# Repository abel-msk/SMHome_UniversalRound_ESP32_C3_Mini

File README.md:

# SMHome_UniversalRound_ESP32_C3_Mini

This is small pcb board was designed to place  under wall mounted electric components in socket box, 
it steel can bee plcad in its own box  znd powered by usb.

## Haw to use

```
git clone https://github.com/abel-msk/SMHome_UniversalRound_ESP32_C3_Mini.git
cd SMHome_UniversalRound_ESP32_C3_Mini
```
Next step is to open project file  `SMHome_UniversalRound_ESP32_C3_Mini_v3.kicad_pro`  in KiKad. 

## 3D view on top of board

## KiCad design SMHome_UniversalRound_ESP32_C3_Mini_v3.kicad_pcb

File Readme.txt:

Универсальная плата с выводами на Дисплей (SPI),  I2C, и 3х GPIO/ADC

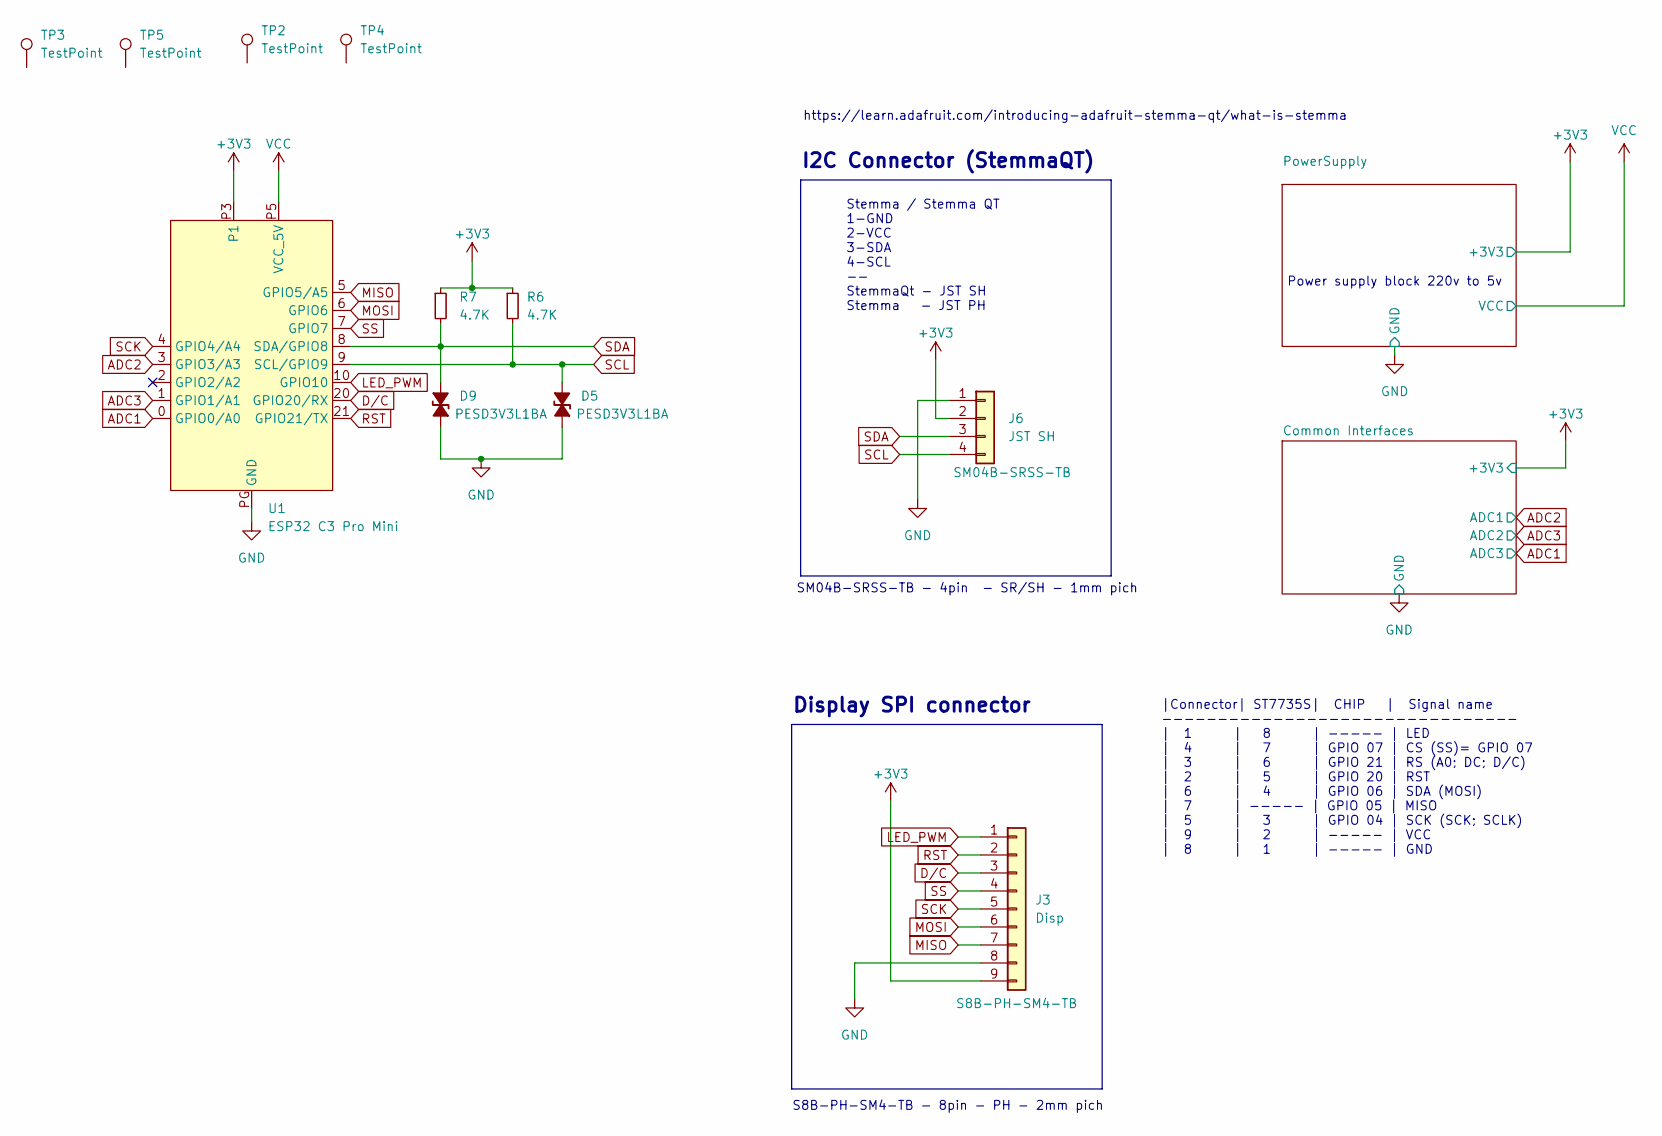
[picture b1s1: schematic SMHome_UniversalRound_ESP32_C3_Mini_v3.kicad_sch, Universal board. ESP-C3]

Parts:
D5, D9: PESD3V3L1BA; D_SOD-323_HandSoldering
J3: Disp; JST_PH_S9B-PH-SM4-TB_1x09-1MP_P2.00mm_Horizontal
J6: JST SH; JST_SH_SM04B-SRSS-TB_1x04-1MP_P1.00mm_Horizontal
R6, R7: 4.7K; R_0805_2012Metric_Pad1.20x1.40mm_HandSolder
TP2, TP3, TP4, TP5: TestPoint; TestPoint_THTPad_D2.0mm_Drill1.0mm
U1: ESP32 C3 Pro Mini; ESP32-C3_Pro_mini_no_keepout

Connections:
+3V3: J3.9, J6.2, R6.1, R7.1, U1.P3 (P1); also elsewhere on the board
ADC1: U1.0 (GPIO0/A0); also elsewhere on the board
ADC2: U1.3 (GPIO3/A3); also elsewhere on the board
ADC3: U1.1 (GPIO1/A1); also elsewhere on the board
D/C: J3.3, U1.20 (GPIO20/RX)
GND: D5.2 (A), D9.2 (A), J3.8, J6.1, U1.PG (GND); also elsewhere on the board
LED_PWM: J3.1, U1.10 (GPIO10)
MISO: J3.7, U1.5 (GPIO5/A5)
MOSI: J3.6, U1.6 (GPIO6)
RST: J3.2, U1.21 (GPIO21/TX)
SCK: J3.5, U1.4 (GPIO4/A4)
SCL: D5.1 (K), J6.4, R6.2, U1.9 (SCL/GPIO9)
SDA: D9.1 (K), J6.3, R7.2, U1.8 (SDA/GPIO8)
SS: J3.4, U1.7 (GPIO7)
VCC: U1.P5 (VCC_5V); also elsewhere on the board

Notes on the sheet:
SM04B-SRSS-TB - 4pin - SR/SH - 1mm pich
Stemma / Stemma QT 1-GND 2-VCC 3-SDA 4-SCL -- StemmaQt - JST SH Stemma - JST PH
Power supply block 220v to 5v
https://learn.adafruit.com/introducing-adafruit-stemma-qt/what-is-stemma
S8B-PH-SM4-TB - 8pin - PH - 2mm pich
I2C Connector (StemmaQT)
|Connector| ST7735S| CHIP | Signal name -------------------------------- | 1 | 8 | ----- | LED | 4 | 7 | GPIO 07 | CS (SS)= GPIO 07 | 3 | 6 | GPIO 21 | RS (A0; DC; D/C) | 2 | 5 | GPIO 20 | RST | 6 | 4 | GPIO 06 | SDA (MOSI) | 7 | ----- | GPIO 05 | MISO | 5 | 3 | GPIO 04 | SCK (SCK; SCLK) | 9 | 2 | 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
Display SPI connector

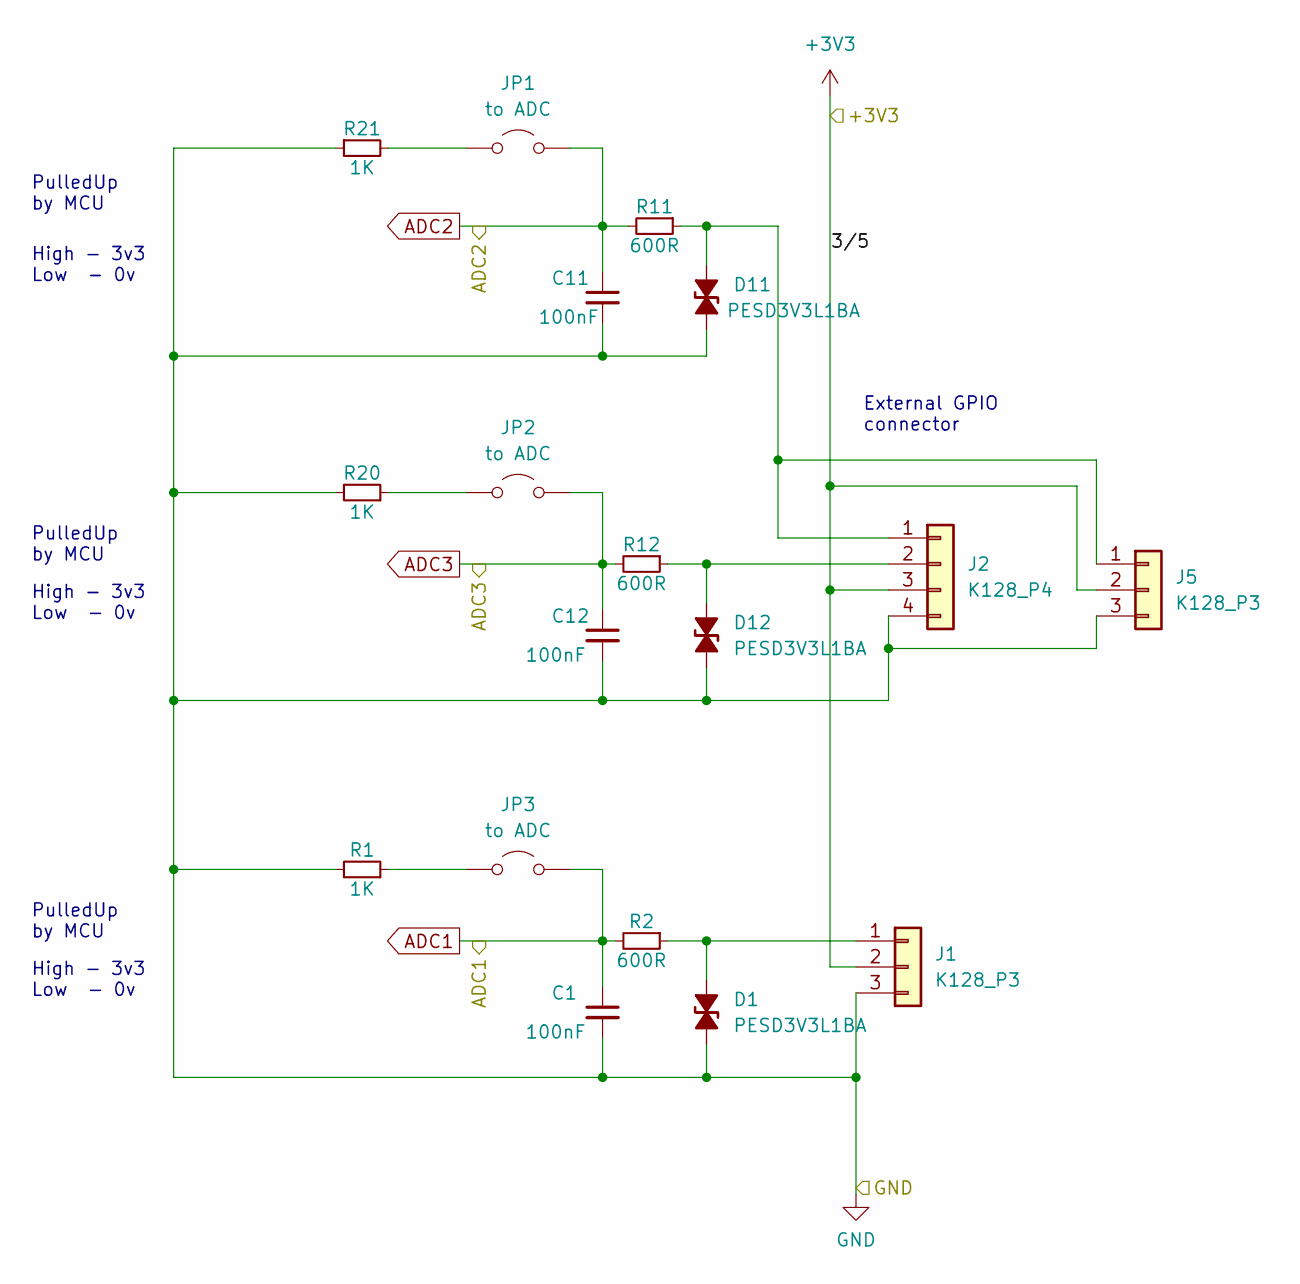
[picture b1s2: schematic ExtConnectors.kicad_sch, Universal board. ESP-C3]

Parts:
C1, C11, C12: 100nF; C_0805_2012Metric
D1, D11, D12: PESD3V3L1BA; D_SOD-323_HandSoldering
J1, J5: K128_P3; PinHeader_1x03_P2.54mm_Vertical
J2: K128_P4; Phoenix Contact_MPT-0,5_4_2,54_P4
JP1, JP2, JP3: to ADC; SolderJumper-2_P1.3mm_Open_TrianglePad1.0x1.5mm
R1, R20, R21: 1K; R_0603_1608Metric_Pad0.98x0.95mm_HandSolder
R2, R11, R12: 600R; R_0603_1608Metric_Pad0.98x0.95mm_HandSolder

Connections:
+3V3: J1.2, J2.3, J5.2; also elsewhere on the board
ADC1: C1.1, JP3.2 (B), R2.2; also elsewhere on the board
ADC2: C11.1, JP1.2 (B), R11.2; also elsewhere on the board
ADC3: C12.1, JP2.2 (B), R12.2; also elsewhere on the board
GND: C1.2, C11.2, C12.2, D1.2 (A), D11.2 (A), D12.2 (A), J1.3, J2.4, J5.3, R1.2, R20.2, R21.1; also elsewhere on the board
unnamed: D1.1 (K), J1.1, R2.1
unnamed: D11.1 (K), J2.1, J5.1, R11.1
unnamed: D12.1 (K), J2.2, R12.1
unnamed: JP1.1 (A), R21.2
unnamed: JP2.1 (A), R20.1
unnamed: JP3.1 (A), R1.1

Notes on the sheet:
External GPIO connector
PulledUp by MCU
High - 3v3 Low - 0v

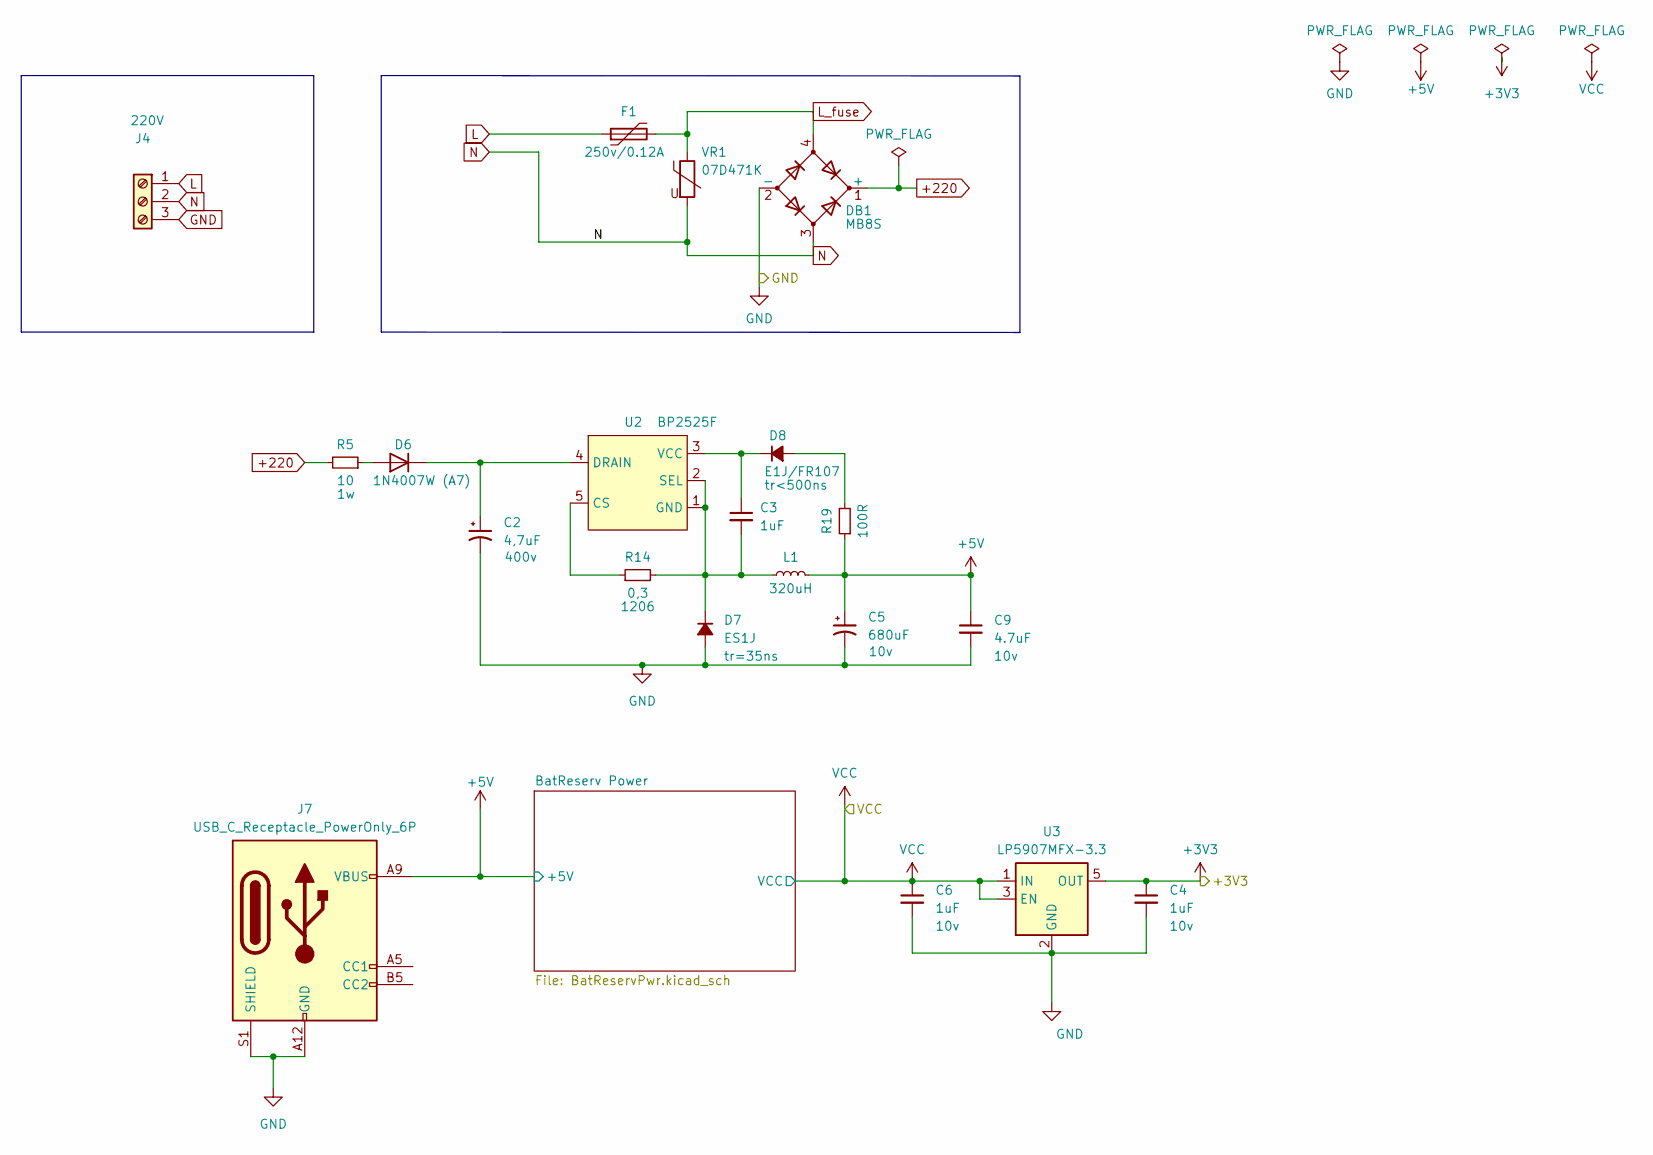
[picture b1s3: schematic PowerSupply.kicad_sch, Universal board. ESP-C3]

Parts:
C2: 4,7uF; CP_Radial_D8.0mm_P3.80mm
C3, C4, C6: 1uF; C_0805_2012Metric_Pad1.18x1.45mm_HandSolder
C5: 680uF; CP_Radial_D6.3mm_P2.50mm
C9: 4.7uF; C_0805_2012Metric_Pad1.18x1.45mm_HandSolder
D6: 1N4007W (A7); D_SOD-123F
D7: ES1J; D_SMA
D8: E1J/FR107; D_SOD-123F
DB1: MB8S; MBS
F1: 250v/0.12A; RF145_D6.5mm_W4mm
J4: 220V; DG301-5.0-03P
J7: USB_C_Receptacle_PowerOnly_6P; USB_C_Receptacle_GCT_USB4125-xx-x_6P_TopMnt_Horizontal
L1: 320uH; L_Radial_D10.0mm_P5.00mm_Fastron_07P
R5: 10; R_Axial_DIN0414_L11.9mm_D4.5mm_P5.08mm_Vertical
R14: 0,3; R_1206_3216Metric_Pad1.30x1.75mm_HandSolder
R19: 100R; R_0805_2012Metric_Pad1.20x1.40mm_HandSolder
U2: BP2525F; SOT33-5
U3: LP5907MFX-3.3; SOT-23-5
VR1: 07D471K; RV_Disc_D9mm_W3.3mm_P5mm

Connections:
+3V3: C4.1, U3.5 (OUT); also elsewhere on the board
+5V: C5.1, C9.1, J7.A9 (VBUS), J7.B9 (VBUS), L1.2, R19.1; also elsewhere on the board
+220: DB1.1 (+), R5.2
GND: C2.2, C4.2, C5.2, C6.2, C9.2, D7.2 (A), DB1.2 (-), J4.3, J7.A12 (GND), J7.B12 (GND), J7.S1 (SHIELD), U3.2 (GND); also elsewhere on the board
L: F1.1, J4.1
L_fuse: DB1.4, F1.2, VR1.1
N: DB1.3, J4.2, VR1.2
unnamed: D6.2 (A), R5.1
unnamed: C2.1, D6.1 (K), U2.4 (DRAIN)
unnamed: C3.2, D7.1 (K), L1.1, R14.2, U2.1 (GND), U2.2 (SEL)
unnamed: D8.2 (A), R19.2
unnamed: C3.1, D8.1 (K), U2.3 (VCC)
unnamed: R14.1, U2.5 (CS)
VCC: C6.1, U3.1 (IN), U3.3 (EN); also elsewhere on the board

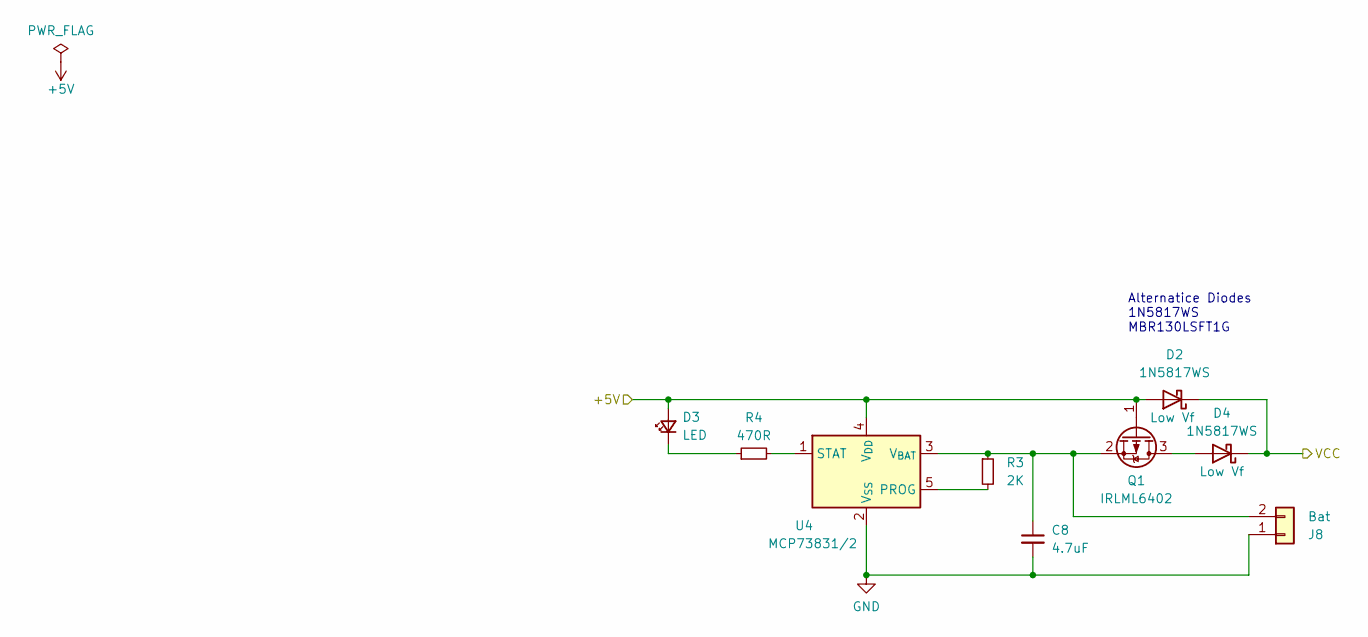
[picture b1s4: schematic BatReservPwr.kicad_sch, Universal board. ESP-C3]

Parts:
C8: 4.7uF; C_0805_2012Metric_Pad1.18x1.45mm_HandSolder
D2, D4: 1N5817WS; D_SOD-123
D3: LED; LED_0603_1608Metric_Pad1.05x0.95mm_HandSolder
J8: Bat; JST_SH_SM02B-SRSS-TB_1x02-1MP_P1.00mm_Horizontal
Q1: IRLML6402; SOT-23
R3: 2K; R_0805_2012Metric_Pad1.20x1.40mm_HandSolder
R4: 470R; R_0805_2012Metric_Pad1.20x1.40mm_HandSolder
U4: MCP73831/2; SOT-23-5

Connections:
+5V: D2.2 (A), D3.2 (A), Q1.1 (G), U4.4 (V_{DD}); also elsewhere on the board
GND: C8.2, J8.1, U4.2 (V_{SS}); also elsewhere on the board
unnamed: D3.1 (K), R4.1
unnamed: D4.2 (A), Q1.3 (D)
unnamed: C8.1, J8.2, Q1.2 (S), R3.1, U4.3 (V_{BAT})
unnamed: R3.2, U4.5 (PROG)
unnamed: R4.2, U4.1 (STAT)
VCC: D2.1 (K), D4.1 (K); also elsewhere on the board

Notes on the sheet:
Alternatice Diodes 1N5817WS MBR130LSFT1G

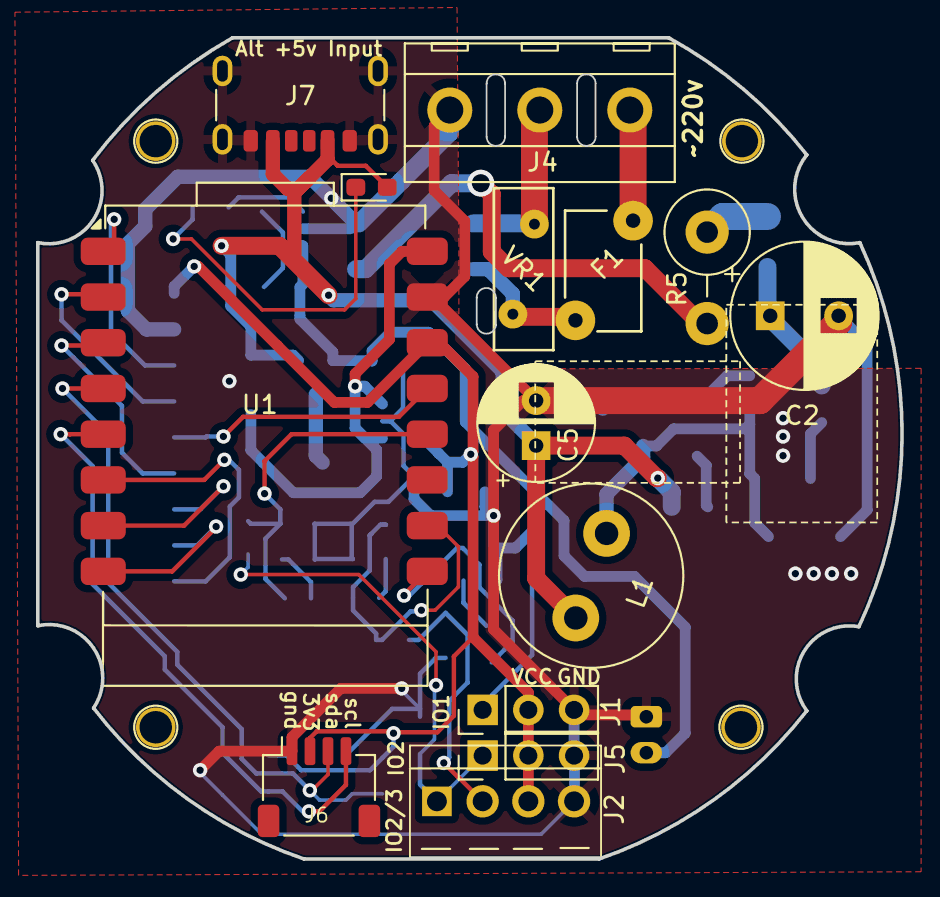
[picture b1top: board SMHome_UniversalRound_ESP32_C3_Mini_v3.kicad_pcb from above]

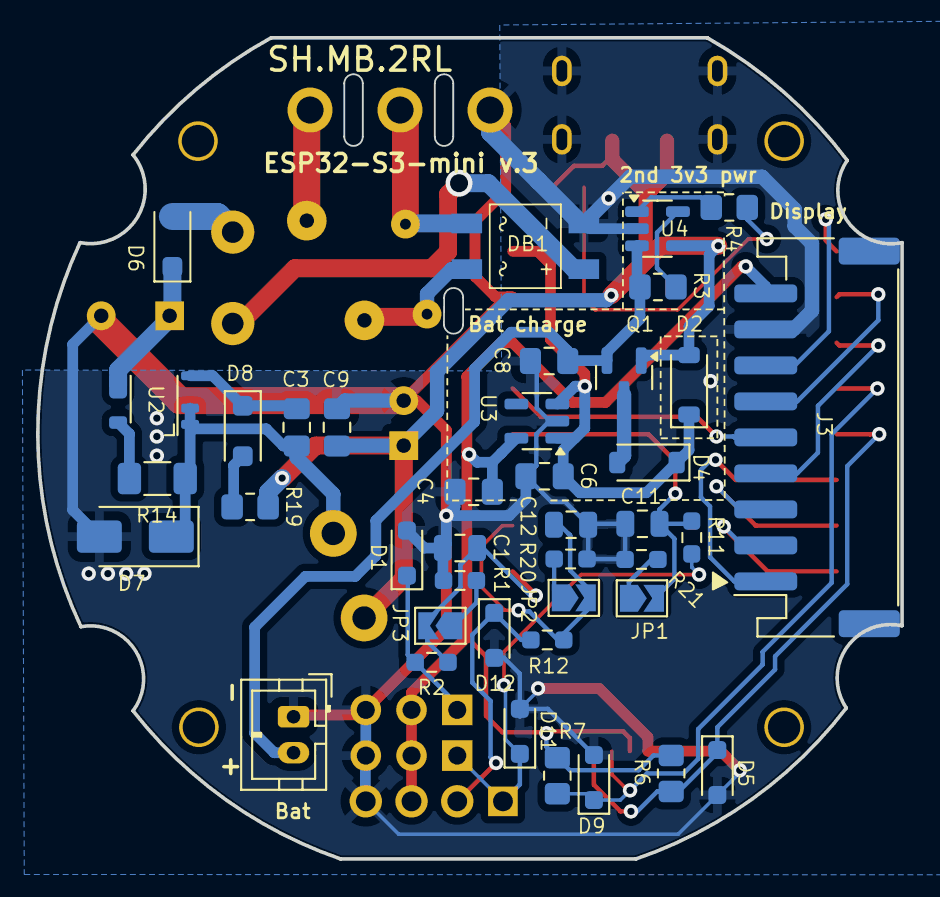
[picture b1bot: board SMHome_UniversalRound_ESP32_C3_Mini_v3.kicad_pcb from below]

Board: 2 copper layers, 48.0 x 45.6 mm, 58 parts (40 on the bottom side), 37 nets.

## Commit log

2025-02-24 Ready for production
2025-02-24 Add production files for nextpcb
2025-11-26 Updated to KiKad 9
2025-11-26 Migrate to KiKad 9
2025-11-26 Update README.md
    Check image insertion
2025-11-26 Update ReadMe file
